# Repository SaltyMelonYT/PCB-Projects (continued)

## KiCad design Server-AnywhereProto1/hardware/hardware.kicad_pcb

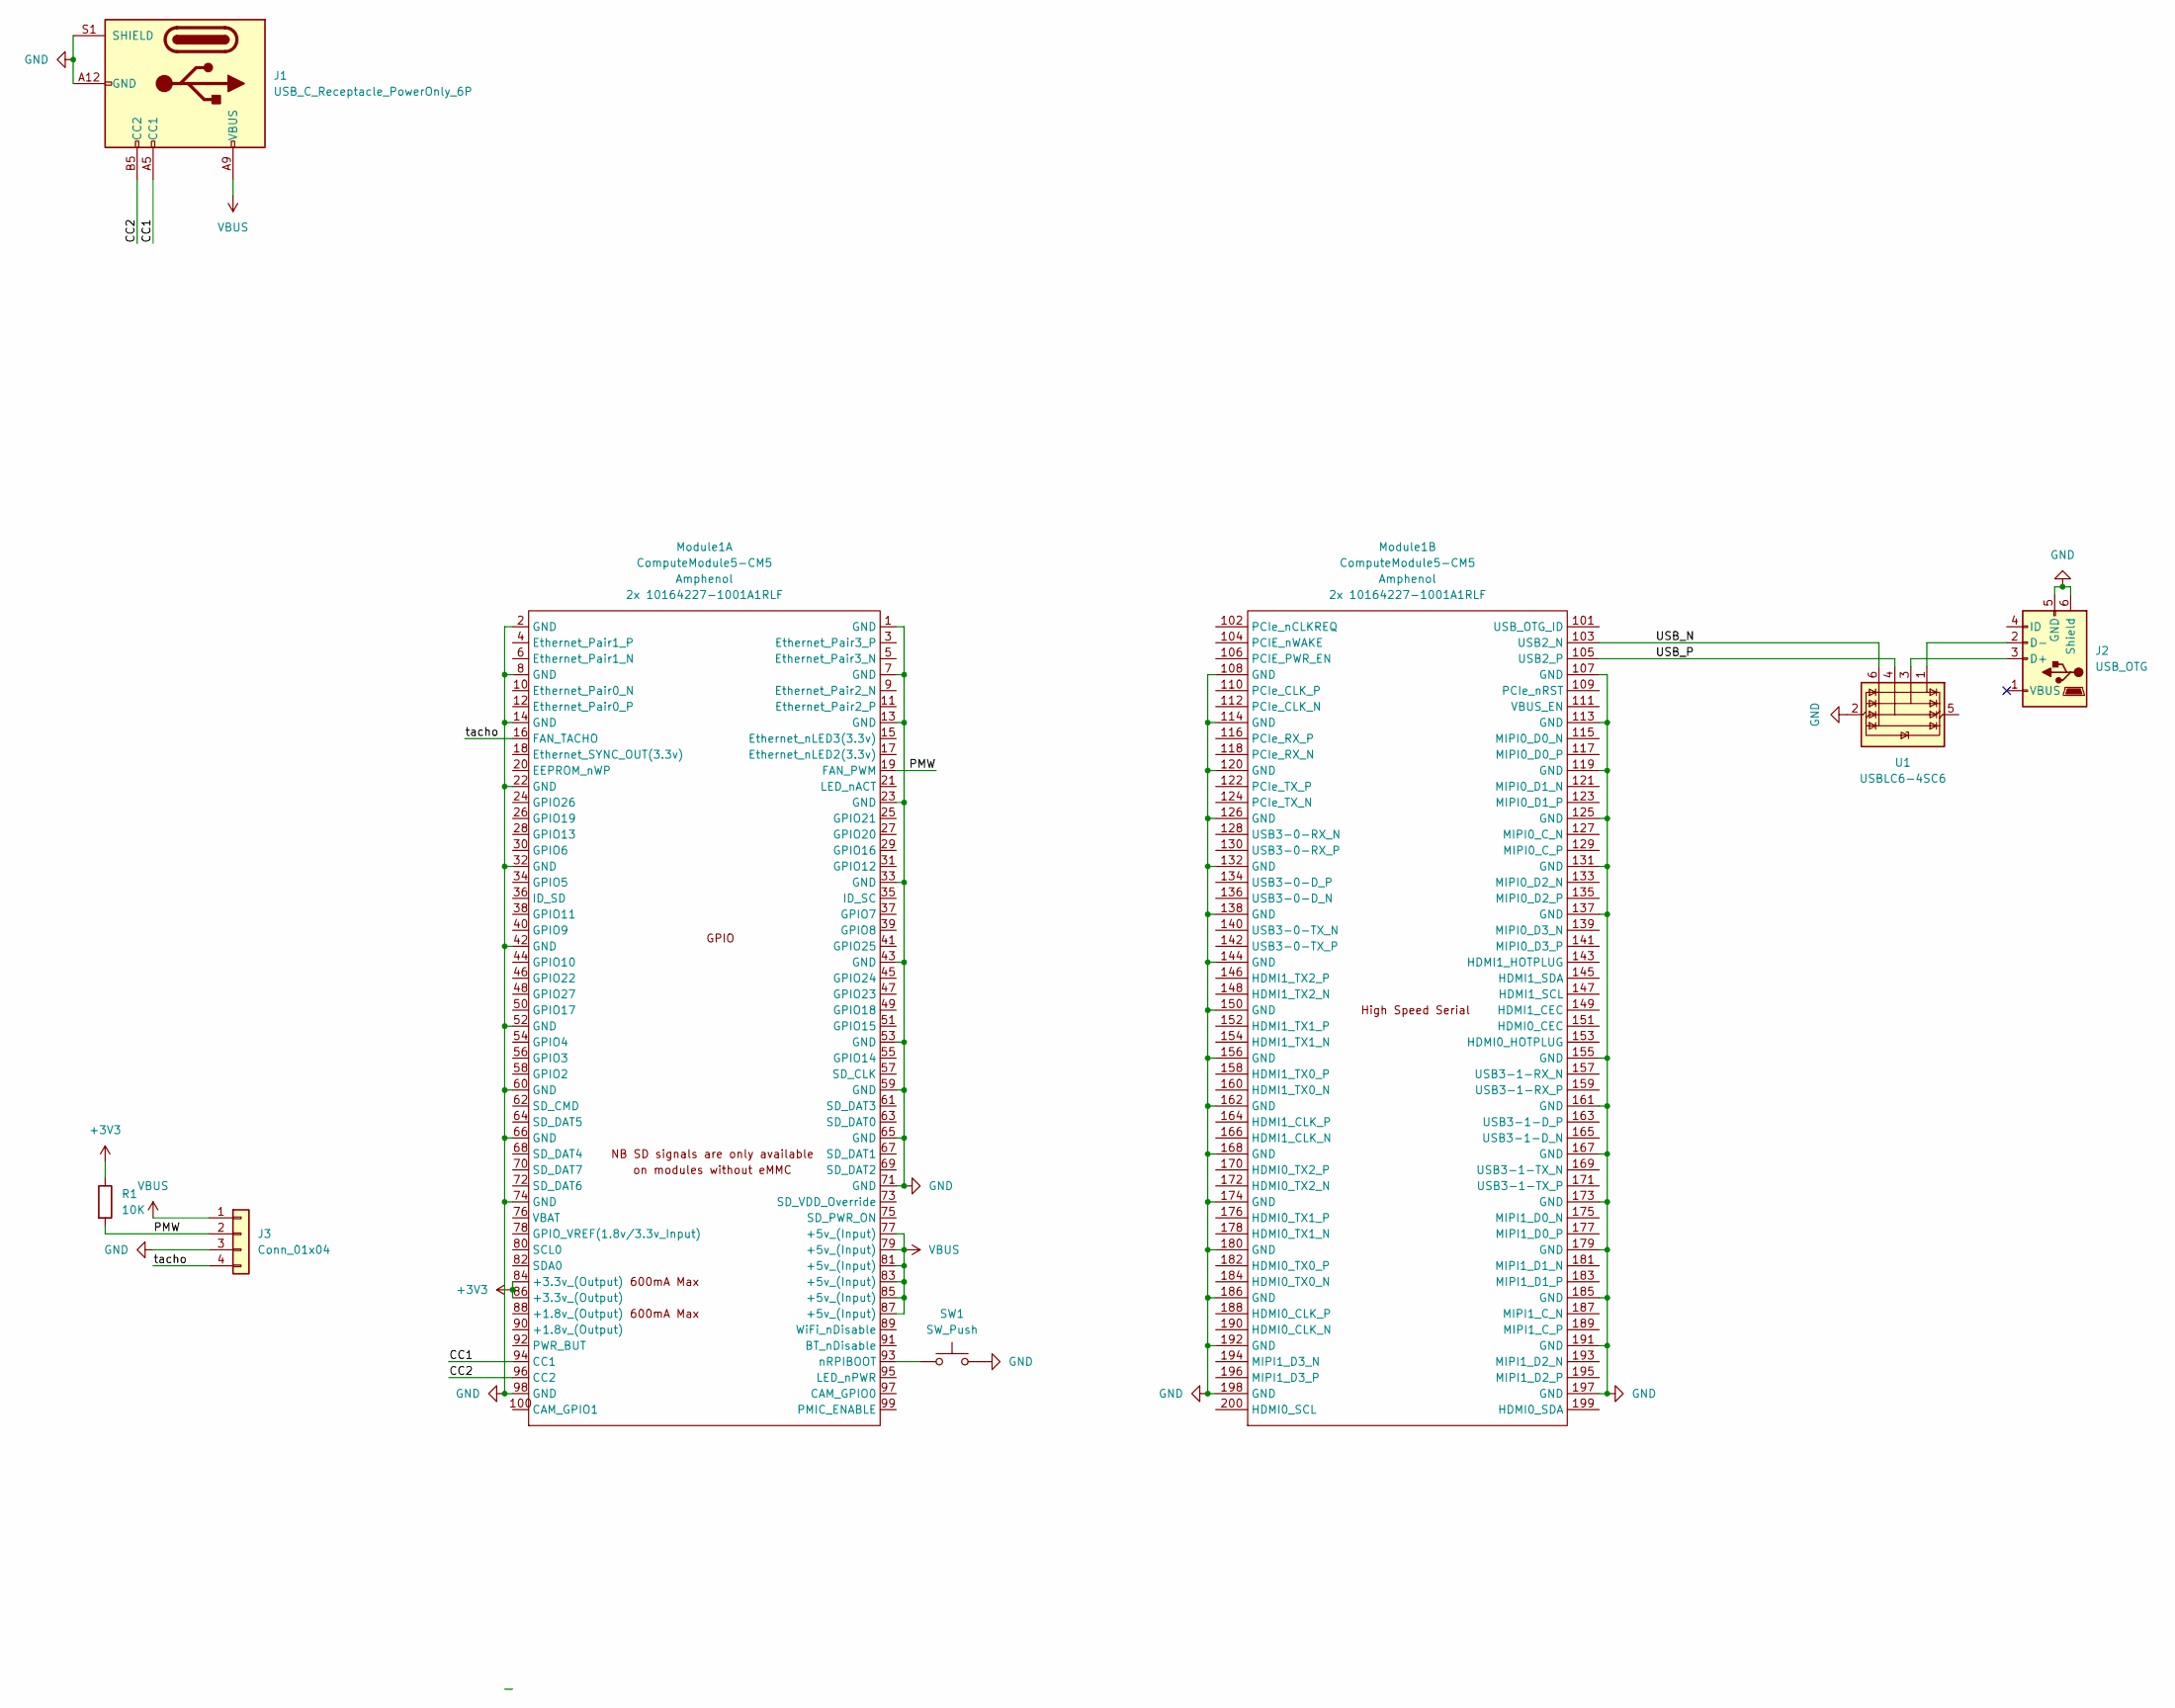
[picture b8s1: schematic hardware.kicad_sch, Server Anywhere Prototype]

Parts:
J1: USB_C_Receptacle_PowerOnly_6P; USB_C_Receptacle_GCT_USB4125-xx-x-0190_6P_TopMnt_Horizontal
J2: USB_OTG; USB_Micro-B_Amphenol_10103594-0001LF_Horizontal
J3: Conn_01x04; JST_SH_BM04B-SRSS-TB_1x04-1MP_P1.00mm_Vertical
Module1: ComputeModule5-CM5; Raspberry-Pi-5-Compute-Module
R1: 10K; R_2512_6332Metric_Pad1.40x3.35mm_HandSolder
SW1: SW_Push; SW_PUSH_6mm
U1: USBLC6-4SC6; SOT-23-6

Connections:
+3V3: Module1.84 (+3.3v_(Output)), Module1.86 (+3.3v_(Output)), R1.1
/CC1: J1.A5 (CC1), Module1.94 (CC1)
/CC2: J1.B5 (CC2), Module1.96 (CC2)
/PMW: J3.2, Module1.19 (FAN_PWM), R1.2
/USB_N: Module1.103 (USB2_N), U1.6 (I/O4)
/USB_P: Module1.105 (USB2_P), U1.4 (I/O3)
/tacho: J3.4, Module1.16 (FAN_TACHO)
GND: J1.A12 (GND), J1.B12 (GND), J1.S1 (SHIELD), J2.5 (GND), J2.6 (Shield), J3.3, Module1.1 (GND), Module1.2 (GND), Module1.7 (GND), Module1.8 (GND), Module1.13 (GND), Module1.14 (GND), Module1.22 (GND), Module1.23 (GND), Module1.32 (GND), Module1.33 (GND), Module1.42 (GND), Module1.43 (GND), Module1.52 (GND), Module1.53 (GND), Module1.59 (GND), Module1.60 (GND), Module1.65 (GND), Module1.66 (GND), Module1.71 (GND), Module1.74 (GND), Module1.98 (GND), Module1.107 (GND), Module1.108 (GND), Module1.113 (GND), Module1.114 (GND), Module1.119 (GND), Module1.120 (GND), Module1.125 (GND), Module1.126 (GND), Module1.131 (GND), Module1.132 (GND), Module1.137 (GND), Module1.138 (GND), Module1.144 (GND), Module1.150 (GND), Module1.155 (GND), Module1.156 (GND), Module1.161 (GND), Module1.162 (GND), Module1.167 (GND), Module1.168 (GND), Module1.173 (GND), Module1.174 (GND), Module1.179 (GND), Module1.180 (GND), Module1.185 (GND), Module1.186 (GND), Module1.191 (GND), Module1.192 (GND), Module1.197 (GND), Module1.198 (GND), SW1.2, U1.2 (GND)
unnamed: J2.3 (D+), U1.3 (I/O2)
unnamed: J2.2 (D-), U1.1 (I/O1)
unnamed: Module1.93 (nRPIBOOT), SW1.1
VBUS: J1.A9 (VBUS), J1.B9 (VBUS), J3.1, Module1.77 (+5v_(Input)), Module1.79 (+5v_(Input)), Module1.81 (+5v_(Input)), Module1.83 (+5v_(Input)), Module1.85 (+5v_(Input)), Module1.87 (+5v_(Input))

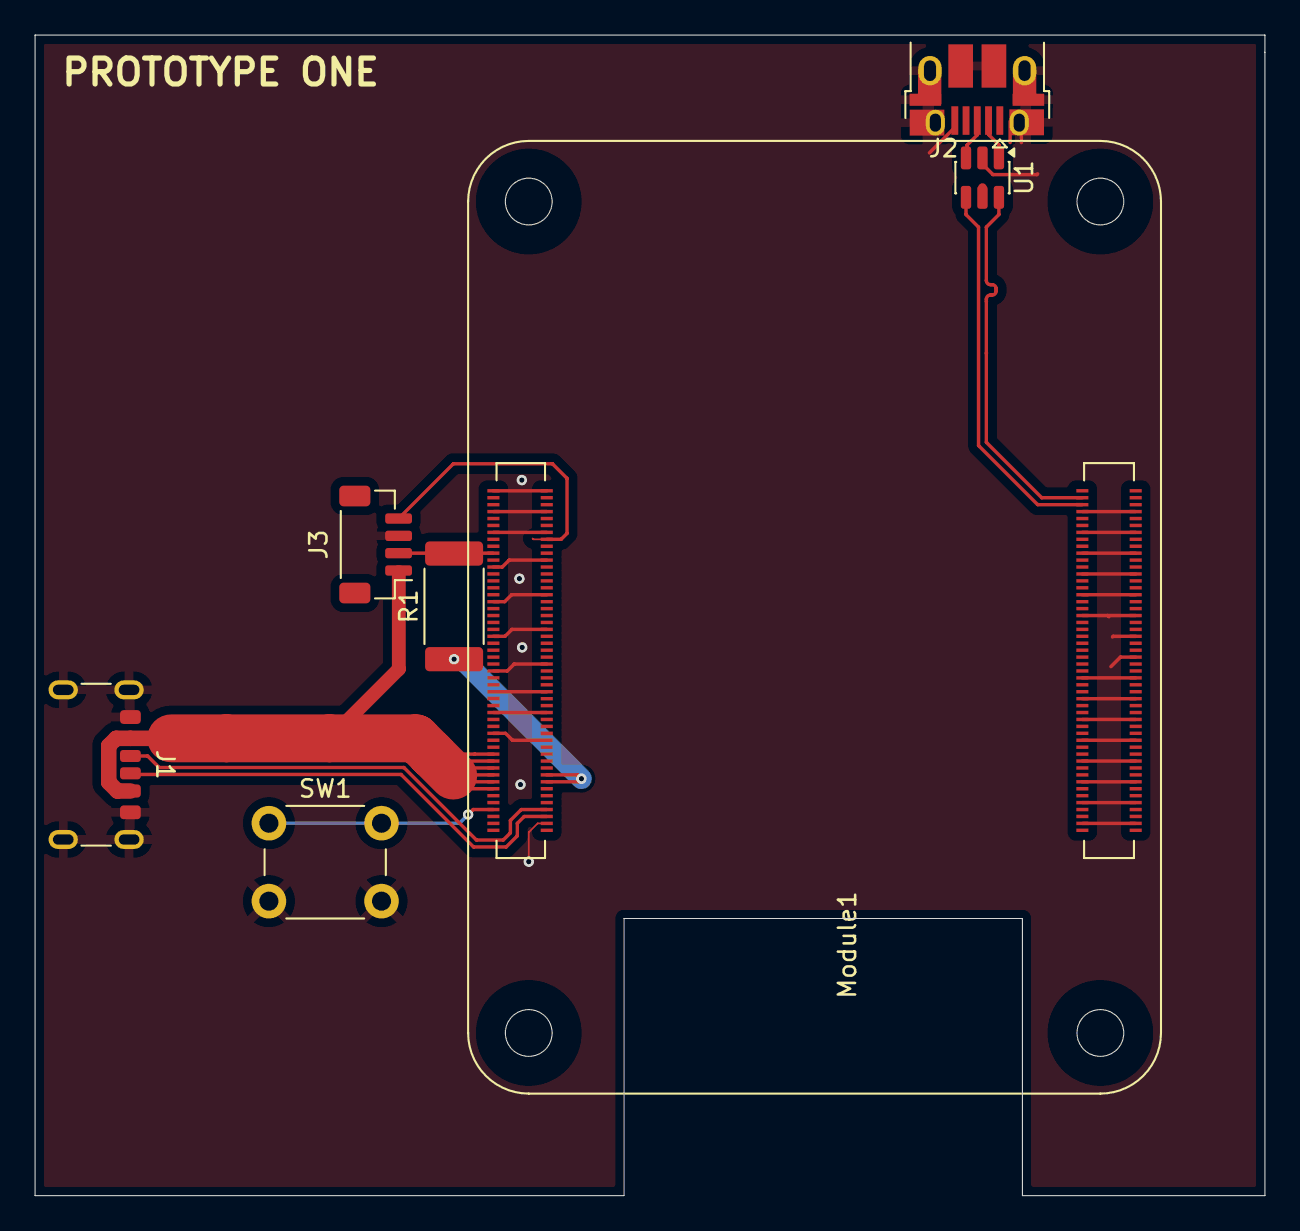
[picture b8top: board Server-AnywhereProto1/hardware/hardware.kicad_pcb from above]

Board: 2 copper layers, 71.0 x 67.0 mm, 7 parts (0 on the bottom side), 12 nets.

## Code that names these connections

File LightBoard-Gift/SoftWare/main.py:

from machine import Pin, PWM
import time

LED1 = 21
LED2 = 20
LED3 = 19
LED4 = 18
LED5 = 17
LED6 = 16
LED7 = 22
LED8 = 15
LED9 = 14
LED10 = 13

SWITCH = 4
BUTTON = 0

led1 = PWM(Pin(LED1))
led2 = PWM(Pin(LED2))
led3 = PWM(Pin(LED3))
led4 = PWM(Pin(LED4))
led5 = PWM(Pin(LED5))
led6 = PWM(Pin(LED6))
led7 = PWM(Pin(LED7))
led8 = PWM(Pin(LED8))
led9 = PWM(Pin(LED9))
led10 = PWM(Pin(LED10))

led1.freq(1000)
led2.freq(1000)
led3.freq(1000)
led4.freq(1000)
led5.freq(1000)
led6.freq(1000)
led7.freq(1000)
led8.freq(1000)
led9.freq(1000)
led10.freq(1000)

button = Pin(BUTTON, Pin.IN, Pin.PULL_UP)
switch = Pin(SWITCH, Pin.IN, Pin.PULL_UP)

mode = 0
last_button_state = 1
debounce_time = 0

def is_switch_on():
    if switch.value() == 0:
        return True
    else:
        led1.duty_u16(0)
        led2.duty_u16(0)
        led3.duty_u16(0)
        led4.duty_u16(0)
        led5.duty_u16(0)
        led6.duty_u16(0)
        led7.duty_u16(0)
        led8.duty_u16(0)
        led9.duty_u16(0)
        led10.duty_u16(0)
        return False

def check_button():
    global mode, last_button_state, debounce_time
    current_state = button.value()
    current_time = time.ticks_ms()
    
    if current_state == 0 and last_button_state == 1:
        if time.ticks_diff(current_time, debounce_time) > 200:
            mode = (mode+1)%3
            debounce_time = current_time
            mode_names = ['Solid', 'Flashing', 'Chase']
            print(f"Mode: {mode_names[mode]}")
    
    last_button_state = current_state

class States:
    @staticmethod
    def solid_mode():
        if not is_switch_on():
            return
        led1.duty_u16(65535)
        led2.duty_u16(65535)
        led3.duty_u16(65535)
        led4.duty_u16(65535)
        led5.duty_u16(65535)
        led6.duty_u16(65535)
        led7.duty_u16(65535)
        led8.duty_u16(65535)
        led9.duty_u16(65535)
        led10.duty_u16(65535)
        time.sleep(0.05)

    @staticmethod
    def flashing_mode():
        if not is_switch_on():
            return
        for duty in range(0, 65536, 512):
            if not is_switch_on():
                return
            led1.duty_u16(duty)
            led2.duty_u16(65535-duty)
            led3.duty_u16(duty)
            led4.duty_u16(65535-duty)
            led5.duty_u16(duty)
            led6.duty_u16(65535-duty)
            led7.duty_u16(duty)
            led8.duty_u16(65535-duty)
            led9.duty_u16(duty)
            led10.duty_u16(65535-duty)

            time.sleep(0.01)
            check_button()
            if mode != 1:
                return
        
        for duty in range(65535, -1, -512):
            if not is_switch_on():
                return
            led1.duty_u16(duty)
            led2.duty_u16(65535-duty)
            led3.duty_u16(duty)
            led4.duty_u16(65535-duty)
            led5.duty_u16(duty)
            led6.duty_u16(65535-duty)
            led7.duty_u16(duty)
            led8.duty_u16(65535-duty)
            led9.duty_u16(duty)
            led10.duty_u16(65535-duty)

            time.sleep(0.01)
            check_button()
            if mode != 1:
                return

    @staticmethod    
    def chase_mode():
        leds = [led1, led2, led3, led4, led5, led6, led7, led8, led9, led10]
        
        while True:
            if not is_switch_on():
                return
                
            for i in range(len(leds)):
                if not is_switch_on():
                    return
                for led in leds:
                    if not is_switch_on():
                        return
                    led.duty_u16(0)

                leds[i].duty_u16(65535)
                time.sleep(0.1)
                check_button()
                if mode != 2:
                    return

try:
    print("Starting - Mode: Solid")
    while True:
        check_button()
        
        if mode == 0:
            States.solid_mode()
        elif mode == 1:
            States.flashing_mode()
        else:
            States.chase_mode()
            
except KeyboardInterrupt:
    led1.duty_u16(0)
    led2.duty_u16(0)
    led3.duty_u16(0)
    led4.duty_u16(0)
    led5.duty_u16(0)
    led6.duty_u16(0)
    led7.duty_u16(0)
    led8.duty_u16(0)
    led9.duty_u16(0)
    led10.duty_u16(0)

    led1.deinit()
    led2.deinit()
    led3.deinit()
    led4.deinit()
    led5.deinit()
    led6.deinit()
    led7.deinit()
    led8.deinit()
    led9.deinit()
    led10.deinit()

    print("LED PWM stopped")

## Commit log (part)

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2025-09-30 Add LightBoard-Gift folder
2025-09-30 Add LightBoard-Gift contents instead of submodule
2025-09-30 Worked on PCB
2025-09-30 I guess I worked on stuff
2025-09-30 Work done so amazing
2025-09-30 Silly additions
2025-09-30 Added a third state
2025-10-01 Work Done
    Completely redesigned the PCB.
    Pico is now on the bottom of the board
    Mounting screw holes added
    Added a "power" switch
    Board got smaller 🥳
    Added resistors to protect LEDs and the Pico.
2025-10-01 Lowkey?
    Forgot to save the files before pushing the last commit
2025-10-01 Bruh
    I didn't save the code whoops
2025-10-02 Additional changes
    Also fixed the function of the on/off switch
2025-10-02 Work Done
    Guess what? YOU GET A 3D MODEL NOW!!!
2025-10-05 New gerbers
2025-10-09 Added case for lightboard
2025-11-05 New PCB project
2025-11-05 Work work work
2025-11-05 README.md
2025-11-05 Images for readme.md
2025-11-05 Add pictures section to README
    Added a section for pictures in the README.
2025-11-05 Namechange for ease
2025-11-05 Reworked the original Lightboard
2025-11-05 Worked on the remaster
    I noticed quite a few things wrong with it so I fixed it.
2025-11-05 Work Hard Play Harder
2025-11-05 Enjoy your new software
2025-11-05 Readme so tuff
2025-11-05 Whoops didn't save the file
2025-11-06 New project in the works
2025-11-06 Worked a little
    I think its far from done but I'm proud of what I have
2025-11-16 Yes twin
2025-11-18 V3 in the works!
2025-12-02 work done we ball
2026-02-13 Holy moly
